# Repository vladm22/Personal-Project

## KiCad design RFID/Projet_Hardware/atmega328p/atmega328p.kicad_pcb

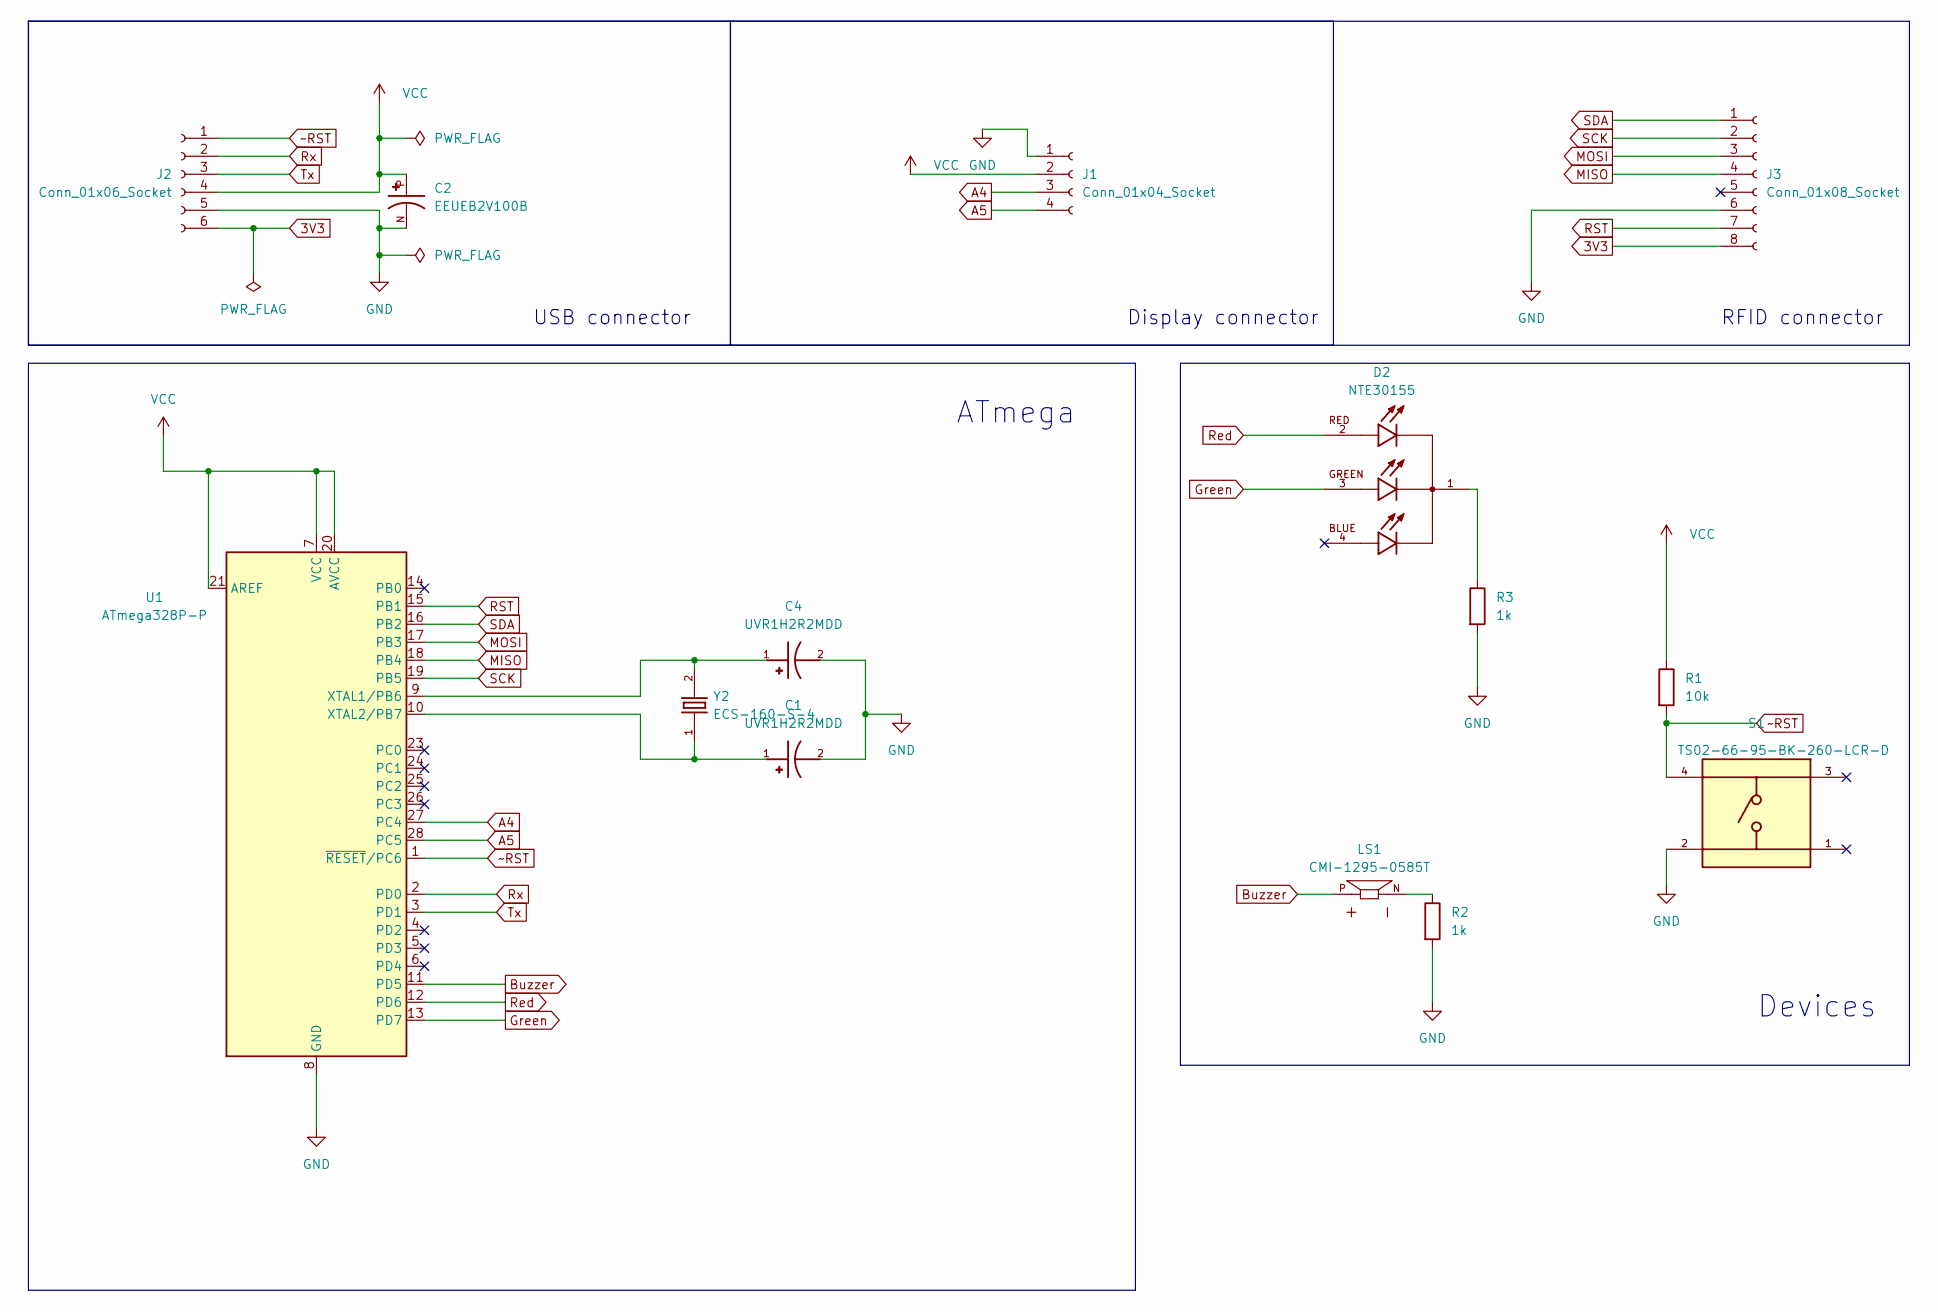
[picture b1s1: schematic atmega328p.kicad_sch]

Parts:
C1, C4: UVR1H2R2MDD; CAPPRD200W50D550H1250; PARTREV NA; DigiKey_Part_Number 493-1100-ND
C2: EEUEB2V100B; CAPPRD500W60D1000H2000; PARTREV 28-FEB-20
D2: NTE30155; LED_NTE30157; PARTREV 3-22; DigiKey_Part_Number 2368-NTE30155-ND
J1: Conn_01x04_Socket; PinSocket_1x04_P2.54mm_Vertical
J2: Conn_01x06_Socket; PinSocket_1x06_P2.54mm_Vertical
J3: Conn_01x08_Socket; PinSocket_1x08_P2.54mm_Vertical
LS1: CMI-1295-0585T; CUI_CMI-1295-0585T; PARTREV N/A
R1: 10k; R_Box_L8.4mm_W2.5mm_P5.08mm
R2, R3: 1k; R_Box_L8.4mm_W2.5mm_P5.08mm
S1: TS02-66-95-BK-260-LCR-D; SW_TS02-66-95-BK-260-LCR-D; PARTREV 1.0
U1: ATmega328P-P; DIP-28_W7.62mm
Y2: ECS-160-S-4; XTAL_ECS-160-20-4X

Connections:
3V3: J2.6, J3.8
A4: J1.3, U1.27 (PC4)
A5: J1.4, U1.28 (PC5)
Buzzer: LS1.P, U1.11 (PD5)
GND: C1.2, C2.N, C4.2, J1.1, J2.5, J3.6, R2.2, R3.2, S1.2, U1.8 (GND), U1.22 (GND)
Green: D2.3, U1.13 (PD7)
MISO: J3.4, U1.18 (PB4)
MOSI: J3.3, U1.17 (PB3)
unnamed: D2.1, R3.1
unnamed: LS1.N, R2.1
unnamed: C4.1, U1.9 (XTAL1/PB6), Y2.2
unnamed: C1.1, U1.10 (XTAL2/PB7), Y2.1
RST: J3.7, U1.15 (PB1)
Red: D2.2, U1.12 (PD6)
Rx: J2.2, U1.2 (PD0)
SCK: J3.2, U1.19 (PB5)
SDA: J3.1, U1.16 (PB2)
Tx: J2.3, U1.3 (PD1)
VCC: C2.P, J1.2, J2.4, R1.1, U1.7 (VCC), U1.20 (AVCC), U1.21 (AREF)
~RST: J2.1, R1.2, S1.4, U1.1 (~RESET/PC6)

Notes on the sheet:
Display connector
USB connector
Devices
ATmega
RFID connector

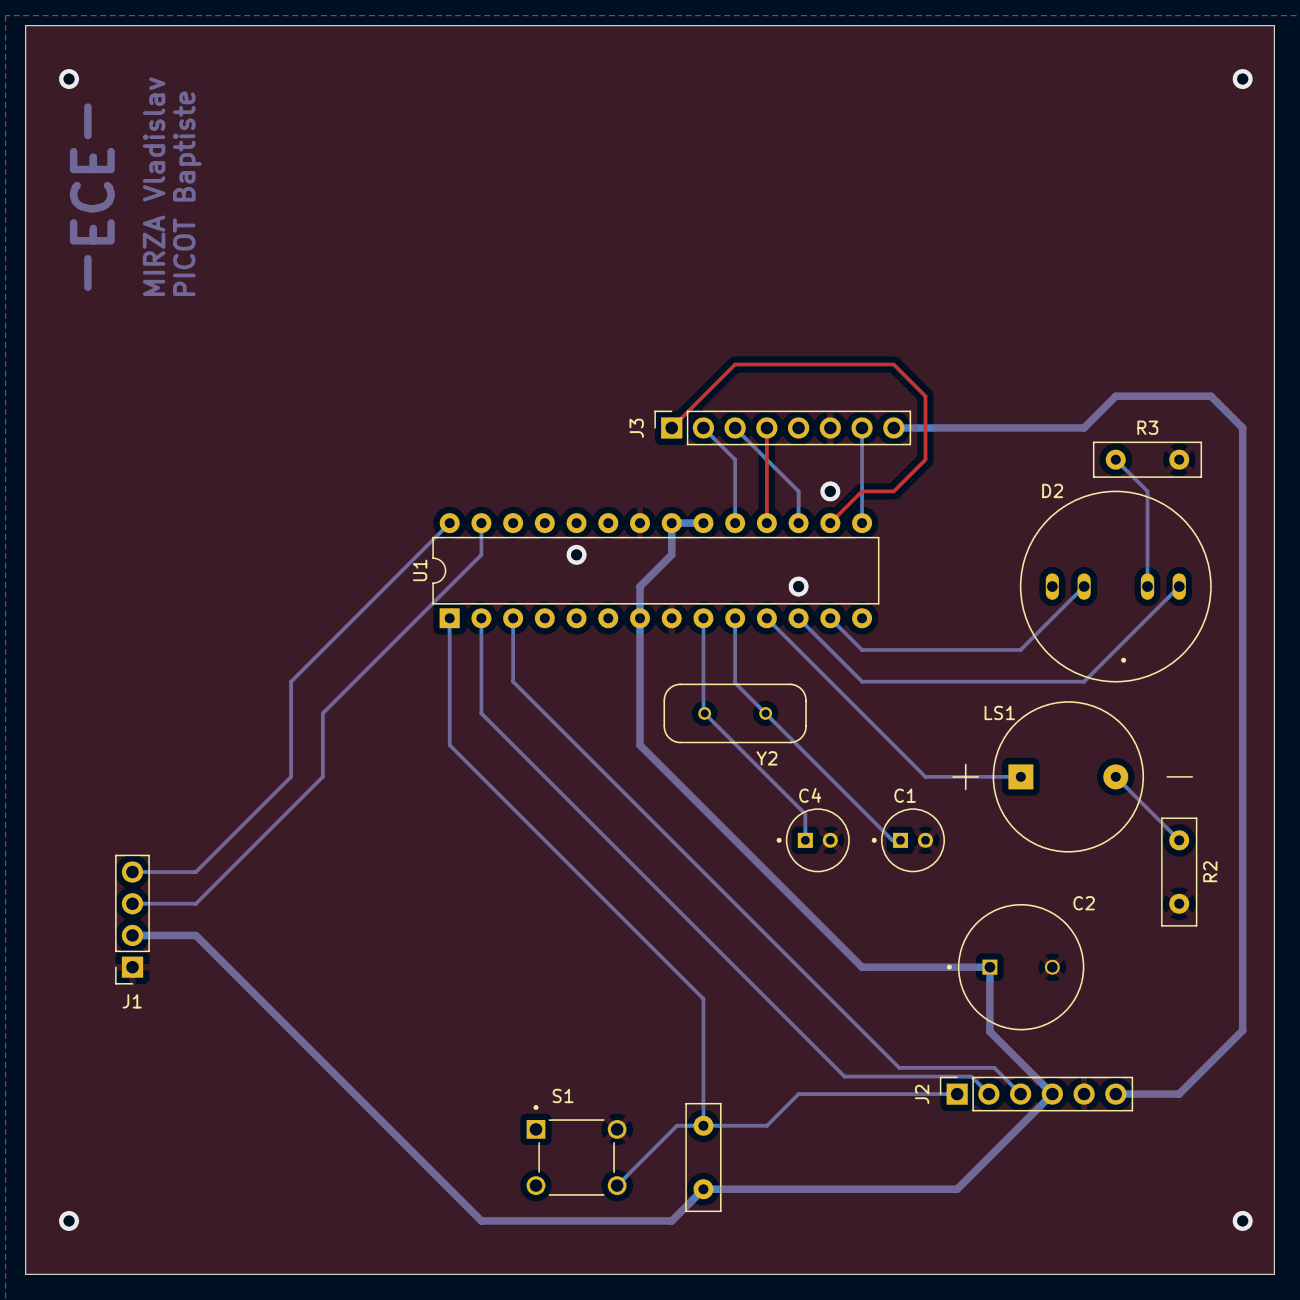
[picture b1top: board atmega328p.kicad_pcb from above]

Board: 2 copper layers, 100.0 x 100.0 mm, 14 parts (0 on the bottom side), 20 nets.

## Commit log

2025-09-17 Add projects
